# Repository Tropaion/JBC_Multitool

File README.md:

# JBC_Multitool
A slot extension device for JBC soldering stations with only one soldering iron terminal.
It is possible to connect:

* 2x soldering iron with the old hirose connector, like the [T210](https://www.weidinger.eu/de/wl13282) and [T245](https://www.weidinger.eu/de/wl13283)
* 2x soldering iron with the newer binder connector, like the [NT115A](https://www.weidinger.eu/de/wl44430) and [AN115A](https://www.weidinger.eu/de/wl45372)

# Hardware
View the latest [PCB Interactive BOM](https://htmlpreview.github.io/?https://github.com/Tropaion/JBC_Multitool/blob/main/hardware/bom/ibom.html) or [KiCad Design](https://kicanvas.org/?github=https%3A%2F%2Fgithub.com%2FTropaion%2FJBC_Multitool%2Fblob%2Fmain%2Fhardware%2FJBC_Multitool.kicad_prodsada).

# Attribution
This project is based on [this project from Lajt](https://lajtronix.eu/2024/02/08/jbc-3-tool-selector/)

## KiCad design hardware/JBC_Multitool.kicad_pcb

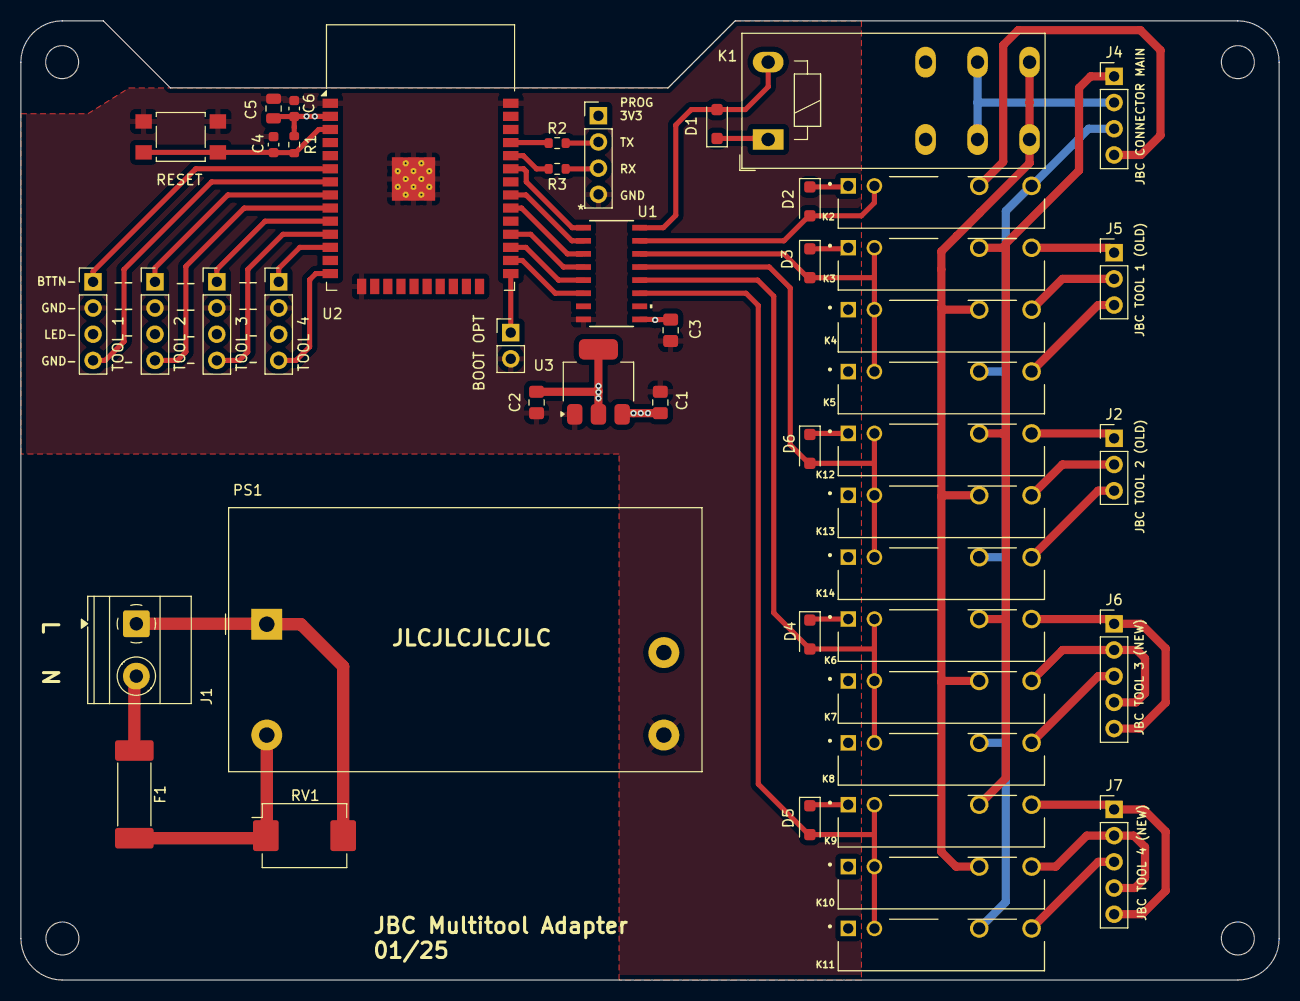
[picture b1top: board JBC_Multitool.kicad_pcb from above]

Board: 2 copper layers, 122.0 x 93.0 mm, 52 parts (0 on the bottom side), 45 nets.

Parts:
BOOT_OPTION1: Conn_01x02; PinHeader_1x02_P2.54mm_Vertical
C1, C2: 1uF/10V; C_0805_2012Metric_Pad1.18x1.45mm_HandSolder
C3: 0.1uF; C_0805_2012Metric_Pad1.18x1.45mm_HandSolder
C4: 1µF/16V/10%; C_0603_1608Metric
C5: 22µF/10V; C_0805_2012Metric
C6: 0.1µF/50V/10%; C_0603_1608Metric
D1, D2, D3, D4, D5, D6: D; D_SOD-123F
ESP_RESET1: SW_Push; SW_SPST_TL3305A
F1: 100mA T; Fuse_Schurter_UMT250
H1, H2, H3, H4: MountingHole; MountingHole_3.2mm_M3
J1: Screw_Terminal_01x02; TerminalBlock_Phoenix_MKDS-1,5-2-5.08_1x02_P5.08mm_Horizont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
J2, J5: Mini XLR6; PinHeader_1x03_P2.54mm_Vertical
J4: Mini XLR6; PinHeader_1x04_P2.54mm_Vertical
J6, J7: Binder 09-0998-00-05; PinHeader_1x05_P2.54mm_Vertical
K1: RT314005; Relay_DPDT_Schrack-RT2-FormC_RM5mm
K2, K3, K4, K5, K6, K7, K8, K9, K10, K11, K12, K13, K14: HF49FD_005-1H12T; HF49FD
PROG1: Conn_01x04; PinHeader_1x04_P2.54mm_Vertical
PS1: IRM-10-5; Converter_ACDC_MeanWell_IRM-10-xx_THT
R1: 10kΩ 1%; R_0603_1608Metric
R2, R3: 160Ω; R_0603_1608Metric
RV1: Varistor 230V; Varistor_Panasonic_VF
SELECT_TOOL_1, SELECT_TOOL_2, SELECT_TOOL_3, SELECT_TOOL_4: Conn_01x04; PinHeader_1x04_P2.54mm_Vertical
U1: TPL7407LDR; D16_TEX
U2: ESP32-WROOM-32
U3: TLV1117-33; SOT-223-3_TabPin2

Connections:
+3.3V: C2.1, C5.2, C6.2, PROG1.1, R1.2, SELECT_TOOL_1.3, SELECT_TOOL_2.3, SELECT_TOOL_3.3, SELECT_TOOL_4.3, U2.2 (VDD), U3.2 (VO)
+5V: C1.1, C3.1, D1.1 (K), D2.1 (K), D3.1 (K), D4.1 (K), D5.1 (K), D6.1 (K), K1.A1, K2.1, K3.1, K4.1, K5.1, K6.1, K7.1, K8.1, K9.1, K10.1, K11.1, K12.1, K13.1, K14.1, PS1.4 (+Vo), U1.9 (COM), U3.3 (VI)
/ESP_RESET: C4.2, ESP_RESET1.2, R1.1, U2.3 (EN)
/GPIO0_BOOT_OPTION: BOOT_OPTION1.1, U2.25 (IO0)
/RELAIS_CARD/TOOL_1_SEL: D3.2 (A), K3.2, K4.2, K5.2, U1.14 (OUT3)
/RELAIS_CARD/TOOL_2_SEL: D6.2 (A), K12.2, K13.2, K14.2, U1.13 (OUT4)
/RELAIS_CARD/TOOL_3_SEL: D4.2 (A), K6.2, K7.2, K8.2, U1.12 (OUT5)
/RELAIS_CARD/TOOL_4_SEL: D5.2 (A), K9.2, K10.2, K11.2, U1.11 (OUT6)
/RELAIS_CARD/TOOL_CODE: K2.4, K5.3, K8.3, K11.3, K14.3
/RELAIS_CARD/TOOL_CODE_SEL: D2.2 (A), K2.2, U1.15 (OUT2)
/RELAIS_CARD/TOOL_POWER: K4.3, K7.3, K10.3, K13.3
/RELAIS_CARD/TOOL_POWER_SEL: D1.2 (A), K1.A2, U1.16 (OUT1)
/RELAIS_CARD/TOOL_SENSOR: J4.1, K3.3, K6.3, K9.3, K12.3
/SELECT_TOOL_1: SELECT_TOOL_1.1, U2.6 (IO34)
/SELECT_TOOL_2: SELECT_TOOL_2.1, U2.8 (IO32)
/SELECT_TOOL_3: SELECT_TOOL_3.1, U2.10 (IO25)
/SELECT_TOOL_4: SELECT_TOOL_4.1, U2.12 (IO27)
/SELECT_TOOL_LED_1: SELECT_TOOL_1.4, U2.7 (IO35)
/SELECT_TOOL_LED_2: SELECT_TOOL_2.4, U2.9 (IO33)
/SELECT_TOOL_LED_3: SELECT_TOOL_3.4, U2.11 (IO26)
/SELECT_TOOL_LED_4: SELECT_TOOL_4.4, U2.14 (IO12)
/TOOL_1_CTRL: U1.3 (IN3), U2.30 (IO18)
/TOOL_2_CTRL: U1.4 (IN4), U2.28 (IO17)
/TOOL_3_CTRL: U1.5 (IN5), U2.27 (IO16)
/TOOL_4_CTRL: U1.6 (IN6), U2.26 (IO4)
/TOOL_POWER_CTRL: U1.1 (IN1), U2.33 (IO21)
/TOOL_SENSOR_CTRL: U1.2 (IN2), U2.31 (IO19)
/UART0_PROG_RX: R3.2, U2.34 (RXD0/IO3)
/UART0_PROG_TX: R2.1, U2.35 (TXD0/IO1)
GND: BOOT_OPTION1.2, C1.2, C2.2, C3.2, C4.1, C5.1, C6.1, ESP_RESET1.1, PROG1.4, PS1.3 (-Vo), SELECT_TOOL_1.2, SELECT_TOOL_2.2, SELECT_TOOL_3.2, SELECT_TOOL_4.2, U1.8 (GND), U2.1 (GND), U2.15 (GND), U2.38 (GND), U2.39 (GND), U3.1 (GND)
unnamed: J1.1, PS1.1 (AC/N), RV1.2
unnamed: F1.1, J1.2
unnamed: J2.1, K12.4
unnamed: J2.2, K13.4
unnamed: J5.1, K3.4
unnamed: J5.2, K4.4
unnamed: J6.1, J6.5, K6.4
unnamed: J6.2, J6.4 (P3), K7.4
unnamed: J6.3, K8.4
unnamed: J7.1, J7.5, K9.4
unnamed: J7.2, J7.4 (P3), K10.4
unnamed: J7.3, K11.4
unnamed: PROG1.2, R2.2
unnamed: PROG1.3, R3.1
unnamed: F1.2, PS1.2 (AC/L), RV1.1

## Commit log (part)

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2025-01-27 kicad files
2025-01-27 readne
2025-01-28 corrected pin numbers on terminal footprint, changed switch-LED configuration
2025-02-01 added 2.nd "old" jbc connector
2025-02-02 changed pcb front silkscreen
2025-02-02 added tool change switch 4
2025-02-04 add gerber and bom
2025-02-04 update bom
2025-02-27 fix pcb
2025-03-30 add firmware
2025-03-31 improve firmeare
2025-12-04 Add files via upload
    PCB und Schaltplan überarbeitet.
    GPIO5 & GPIO14 jetzt „not connected“, da diese GPIOs beim Boot auf HIGH gesetzt werden und die Relais und die LED anschalteten.
2025-12-04 Add files via upload
    main.c angepasst an geänderte/n PCB & Schaltplan.
    GPIO5 & GPIO14 werden nun nicht mehr verwendet.
2025-12-05 new bom and gerber
2025-12-21 improve code, restores last selected tool after reboot
